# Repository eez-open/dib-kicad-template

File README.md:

### KiCad project template for EEZ DIB peripheral modules

The project template makes it easy to start working on a new peripheral module and will need to be copied to your local KiCad template folder.

The template was created using symbols, footprints and 3D models from [eez-kicad-libraries](https://github.com/eez-open/eez-kicad-libraries), so for proper display it is recommended to install that plugin.

### Setting up the KiCad template folder

Start KiCad and in `Preferences` (1) open `Configure Paths...` (2) where you can see the currently configured Template path that you can change as desired.

### Copying a template and creating a new project from the template

Copy the complete contents of the template folder from this repository into it (e.g. `v2.0`)

Now you are ready to use the EEZ DIB template for your new project. To do this, you will need to select the `New Project...` option from the `File` menu (3).

Select `User Templates`, and find the EEZ DIB template (4) and confirm the selection with `OK` (5).

### Setting project text variables

The new project is created and you can change the predefined texts as desired by first opening the `Schematic Editor` (6).

In the `File` menu of the Schematic Editor, select the option `Schematic Setup...` (7) and under `Text Variables` (8) you can see the values ​​of the text variables that were used and change them as desired.

Good luck and we wish you successful development. Feel free to keep us updated on your progress and contact us if you need further help with the EEZ DIB!

### About KiCad

KiCad is a Cross-Platform free and Open Source Electronics Design Automation Suite. See [KiCad EDA](https://kicad.org/) for more information.

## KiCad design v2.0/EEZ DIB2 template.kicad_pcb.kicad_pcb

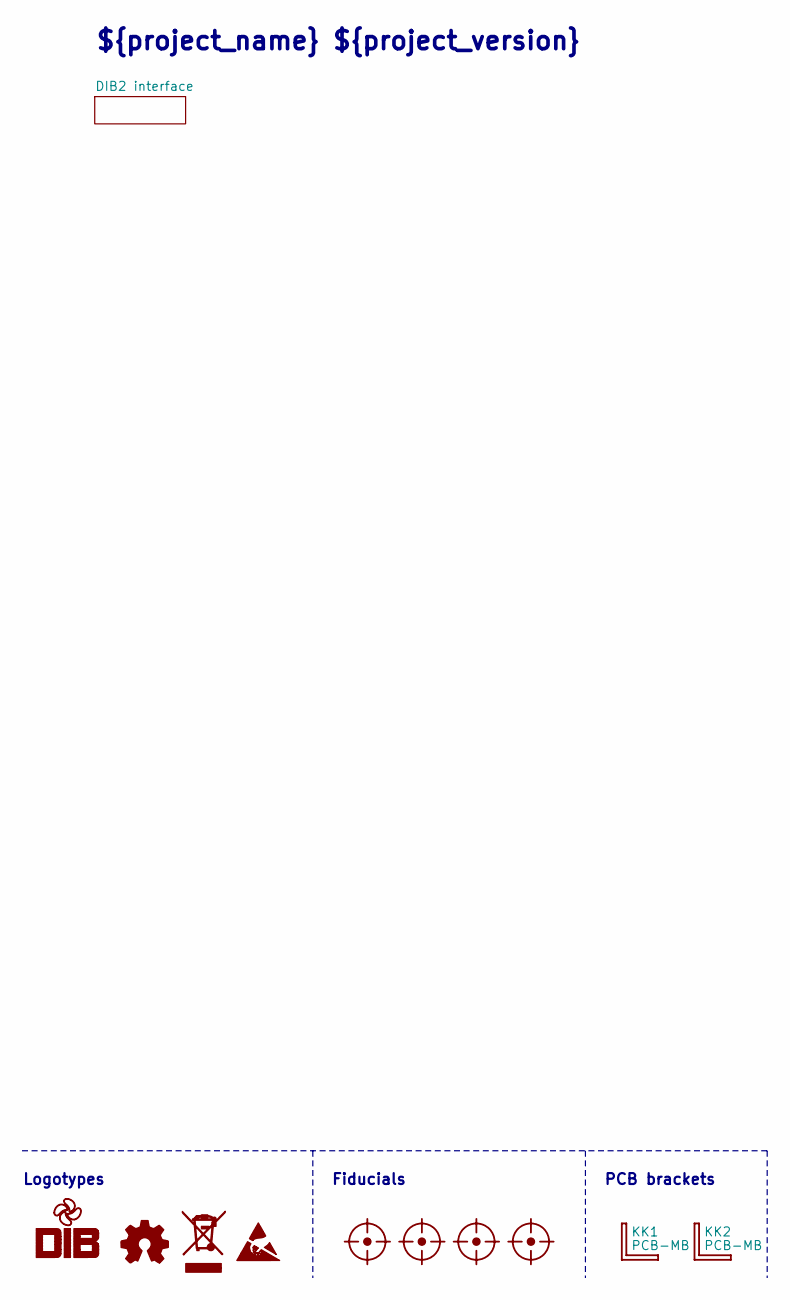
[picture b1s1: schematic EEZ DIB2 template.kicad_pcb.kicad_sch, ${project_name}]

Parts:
FM1, FM2, FM3, FM4: FIDUCIAL_2; Fiducial_0.75mm_Mask1.5mm
KK1, KK2: PCB-MB; PCB-MB-01; DigiKey RPC1760-ND
LOGO1: EEZ DIB logo; EEZ DIB logo (9mm)
LOGO2: Open HW logo
LOGO3: WEEE logo
LOGO4: ESD logo

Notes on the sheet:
${project_name} ${project_version}
PCB brackets
Logotypes
Fiducials

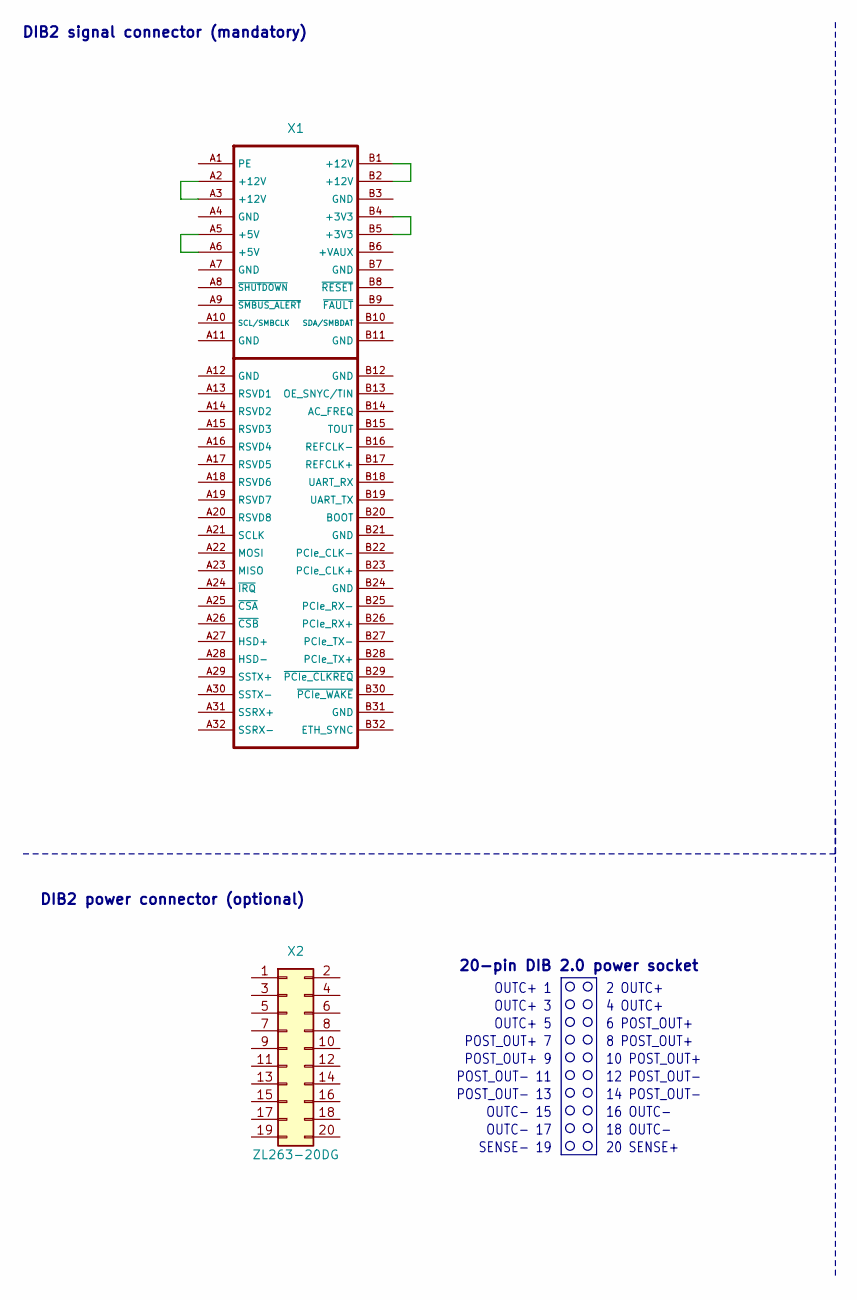
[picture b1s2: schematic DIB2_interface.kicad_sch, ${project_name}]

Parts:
X1: DIB 2.0 signal connector; DIB 2.0 edge card connector
X2: ZL263-20DG; SSW-110-02-T-D-RA; DigiKey SAM10030-ND

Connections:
unnamed: X1.B4 (+3V3), X1.B5 (+3V3)
unnamed: X1.A5 (+5V), X1.A6 (+5V)
unnamed: X1.A2 (+12V), X1.A3 (+12V)
unnamed: X1.B1 (+12V), X1.B2 (+12V)

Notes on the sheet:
16 OUTC-
OUTC+ 3
OUTC+ 5
POST_OUT- 13
14 POST_OUT-
DIB2 signal connector (mandatory)
POST_OUT+ 7
12 POST_OUT-
POST_OUT+ 9
POST_OUT- 11
OUTC+ 1
4 OUTC+
OUTC- 17
20-pin DIB 2.0 power socket
OUTC- 15
20 SENSE+
SENSE- 19
6 POST_OUT+
8 POST_OUT+
10 POST_OUT+
18 OUTC-
DIB2 power connector (optional)
2 OUTC+

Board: 4 copper layers, 12 parts (0 on the bottom side), 4 nets, no tracks yet.

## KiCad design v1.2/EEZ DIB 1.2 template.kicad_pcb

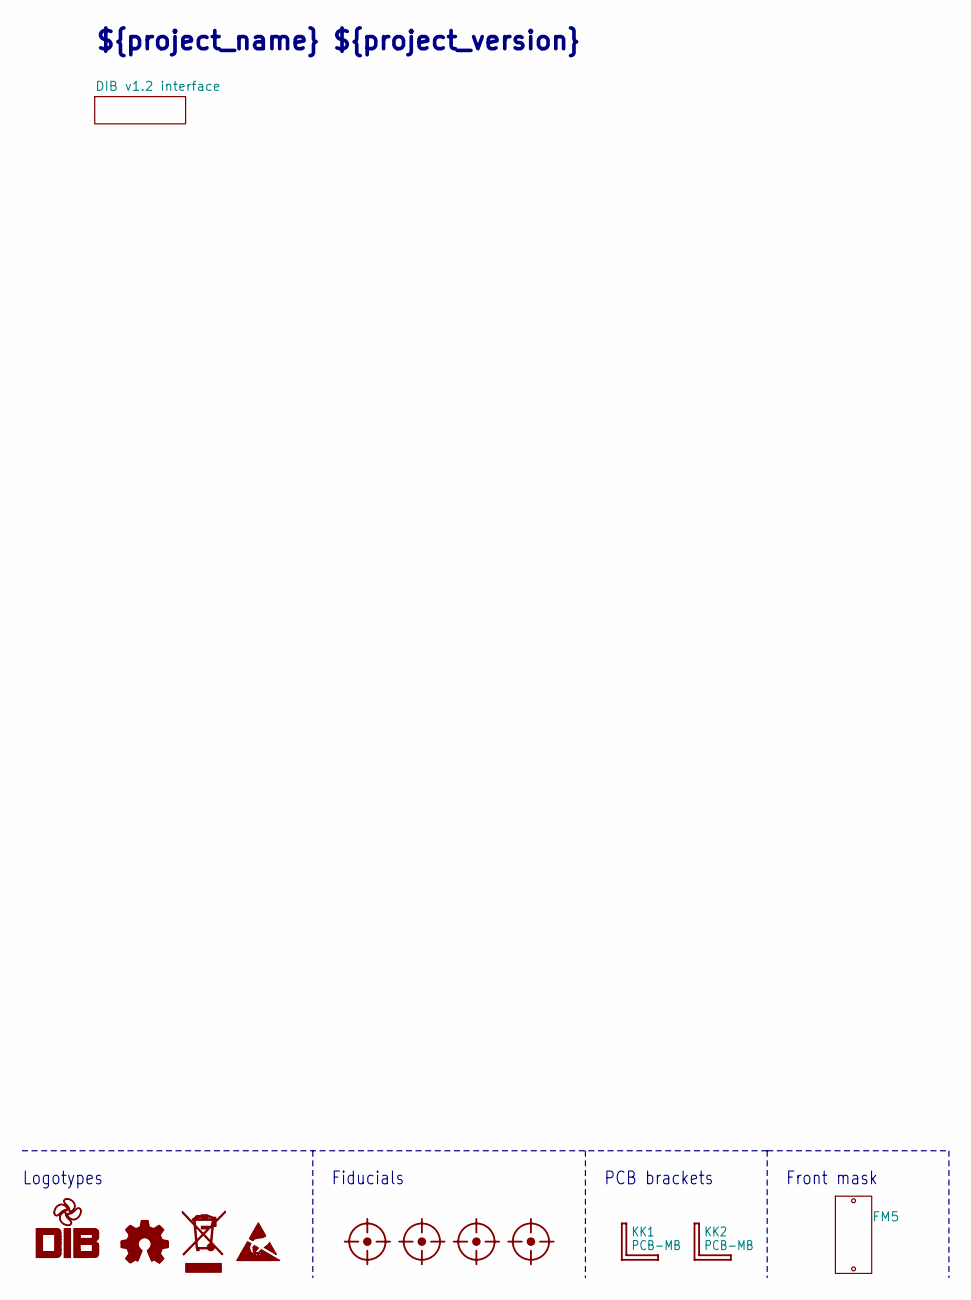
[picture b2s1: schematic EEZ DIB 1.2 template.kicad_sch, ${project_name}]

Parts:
FM1, FM2, FM3, FM4: FIDUCIAL_2; Fiducial
FM5: DIB module front mask
KK1, KK2: PCB-MB; PCB-MB-01; DigiKey RPC1760-ND
LOGO1: EEZ DIB logo; EEZ DIB logo (9mm)
LOGO2: Open HW logo
LOGO3: WEEE logo
LOGO4: ESD logo

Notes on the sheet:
${project_name} ${project_version}
PCB brackets
Logotypes
Fiducials
Front mask

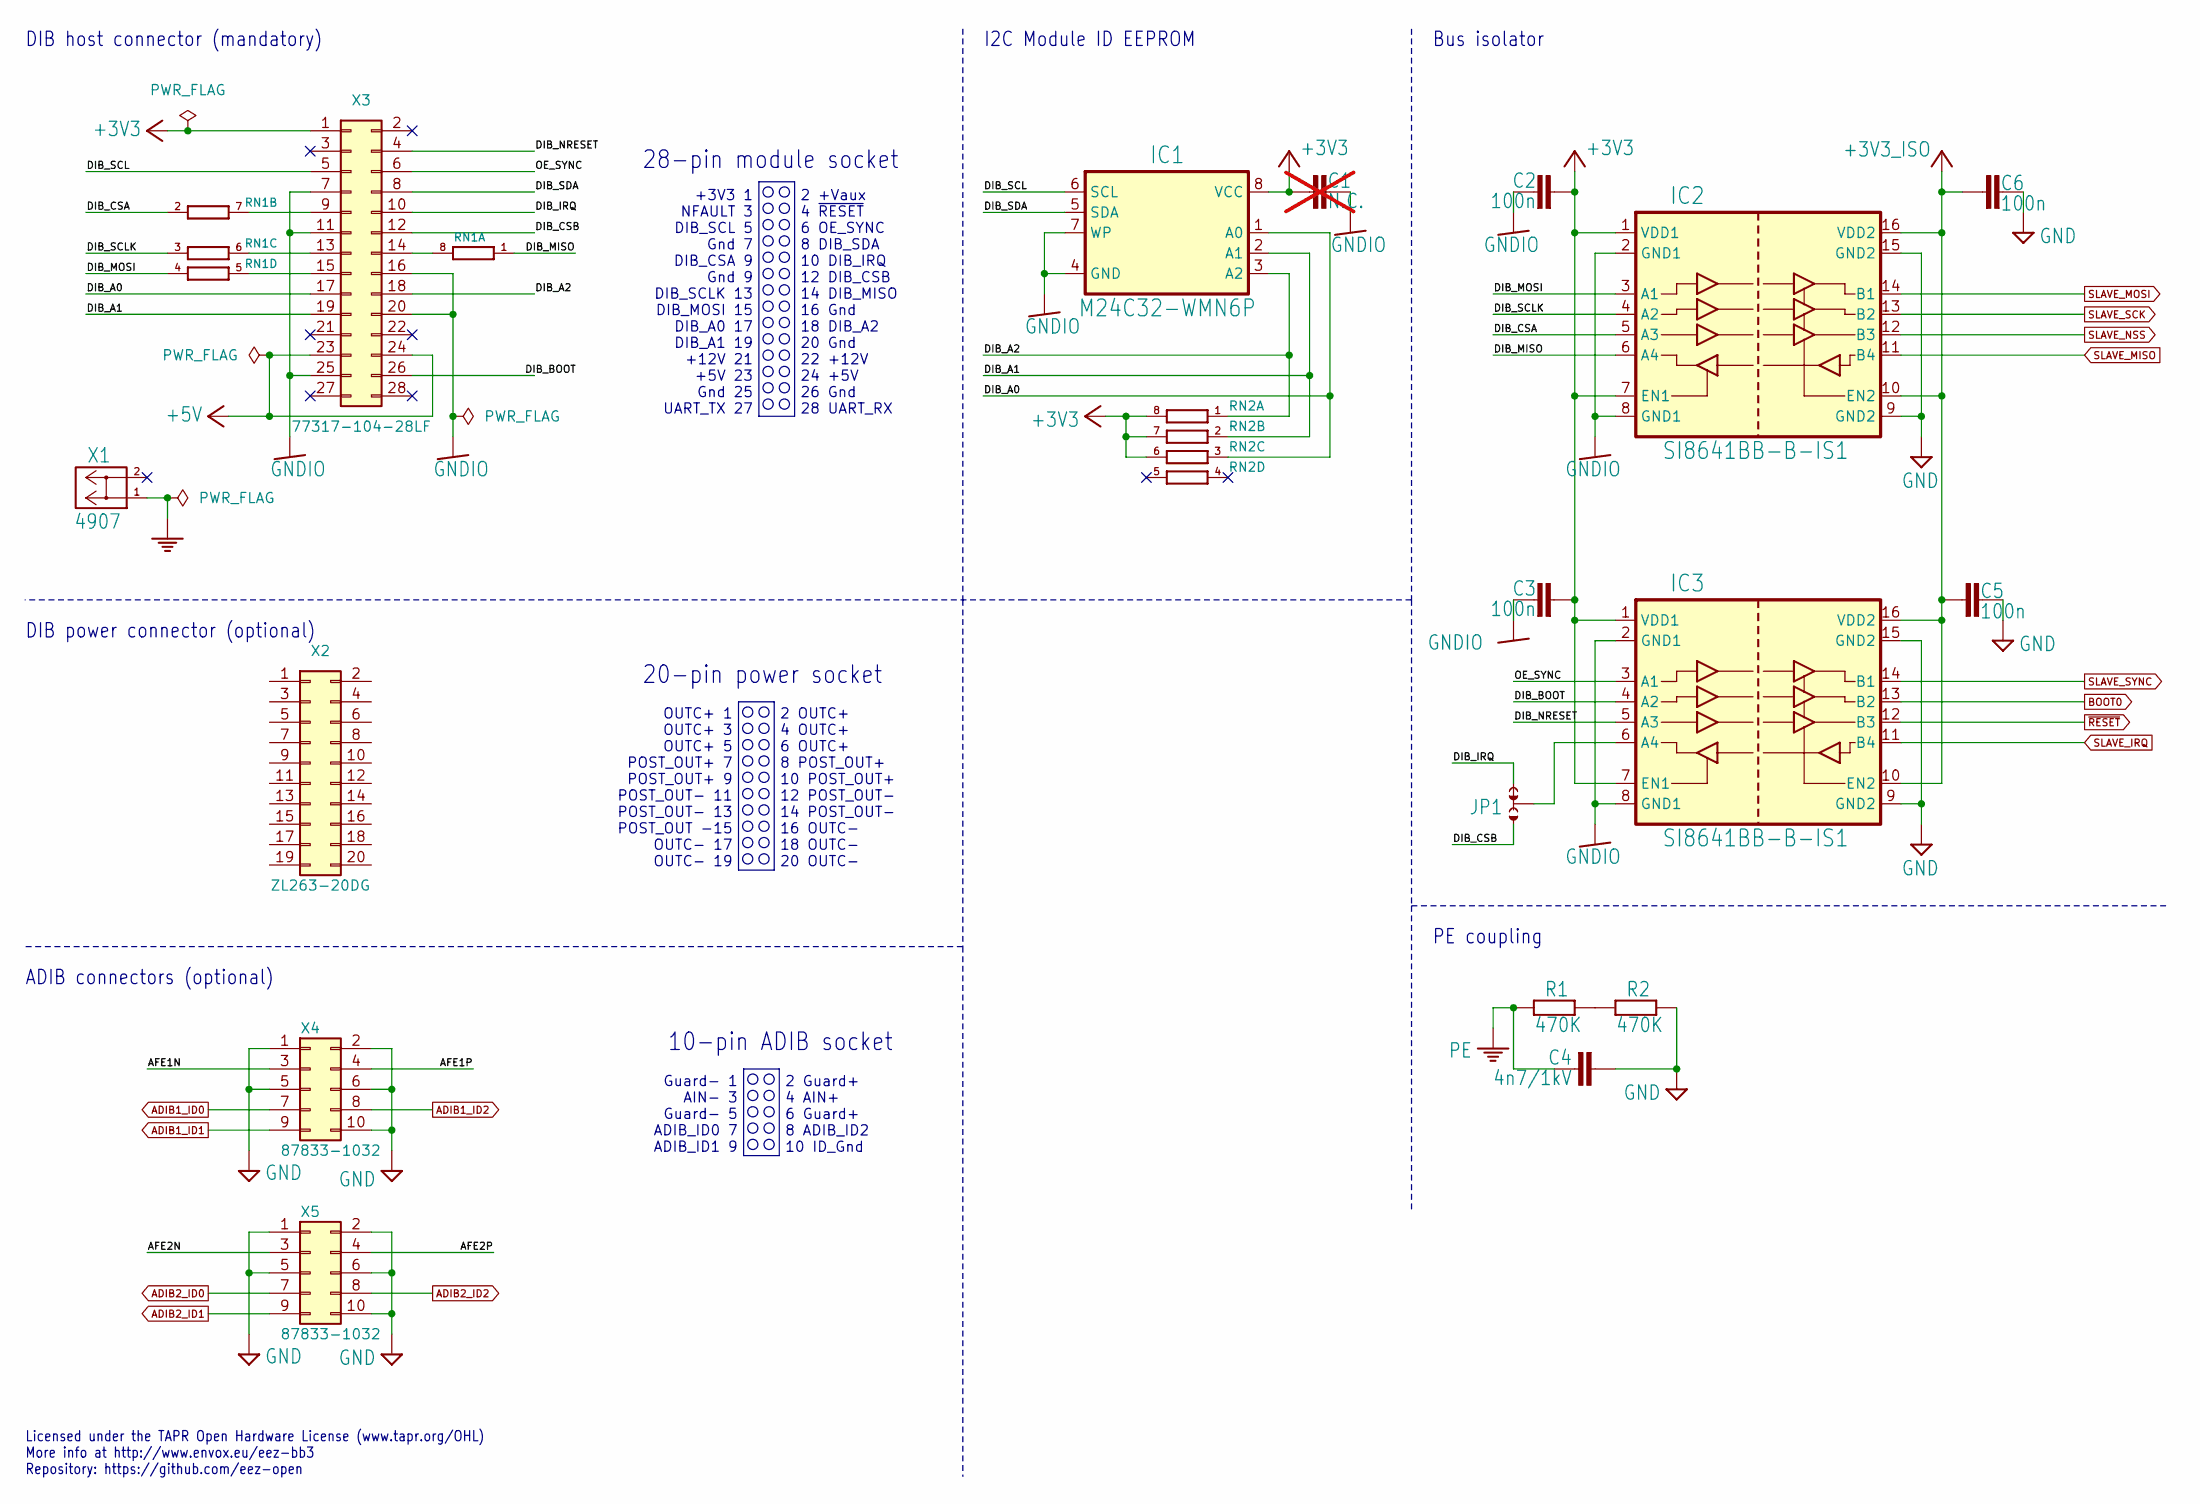
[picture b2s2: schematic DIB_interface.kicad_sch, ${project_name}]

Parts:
C1: N.C.; C_0603_1608Metric; not fitted
C2, C3, C5, C6: 100n; C_0603_1608Metric; DigiKey 1276-1005-2-ND
C4: 4n7/1kV; C_1206_3216Metric; DigiKey 732-12074-2-ND
IC1: M24C32-WMN6P; SOIC127P600X173-8N; DigiKey 497-8572-5-ND
IC2, IC3: SI8641BB-B-IS1; SOIC127P600X265-16N; DigiKey 336-2566-ND
JP1: JP3-CUT-0805-ROTATED; JP3 shorted
R1, R2: 470K; R_0805_2012Metric; DigiKey 13-RT0805FRE07470KLDKR-ND
RN1: DR1206-33R-4/8; CAY16; DigiKey CAY16-330J4LFCT-ND
RN2: DR1206-47K-4/8; CAY16; DigiKey CAY16-330J4LFCT-ND
X1: 4907; DigiKey 36-4907-ND
X2: ZL263-20DG; SSW-110-02-T-D-RA; DigiKey SAM10030-ND
X3: 77317-104-28LF; DigiKey S2111EC-14-ND
X4, X5: 87833-1032; DS1014-10RF1B; DigiKey WM8615-ND

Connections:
+3V3: C1.2, C2.1, C3.1, IC1.8 (VCC), IC2.1 (VDD1), IC2.7 (EN1), IC3.1 (VDD1), IC3.7 (EN1), RN2.6 (2), RN2.7 (2), RN2.8 (2), X3.1
+3V3_ISO: C5.2, C6.2, IC2.10 (EN2), IC2.16 (VDD2), IC3.10 (EN2), IC3.16 (VDD2)
+5V: X3.23, X3.24
/DIB v1.2 interface/AFE1N: X4.3
/DIB v1.2 interface/AFE1P: X4.4
/DIB v1.2 interface/AFE2N: X5.3
/DIB v1.2 interface/AFE2P: X5.4
/DIB v1.2 interface/DIB_A0: IC1.1 (A0), RN2.3 (1), X3.17
/DIB v1.2 interface/DIB_A1: IC1.2 (A1), RN2.2 (1), X3.19
/DIB v1.2 interface/DIB_A2: IC1.3 (A2), RN2.1, X3.18
/DIB v1.2 interface/DIB_BOOT: IC3.4 (A2), X3.26
/DIB v1.2 interface/DIB_CSA: IC2.5 (A3), RN1.2 (1)
/DIB v1.2 interface/DIB_CSB: JP1.NO, X3.12
/DIB v1.2 interface/DIB_IRQ: JP1.NC, X3.10
/DIB v1.2 interface/DIB_MISO: IC2.6 (A4), RN1.1
/DIB v1.2 interface/DIB_MOSI: IC2.3 (A1), RN1.4 (1)
/DIB v1.2 interface/DIB_NRESET: IC3.5 (A3), X3.4
/DIB v1.2 interface/DIB_SCL: IC1.6 (SCL), X3.5
/DIB v1.2 interface/DIB_SCLK: IC2.4 (A2), RN1.3 (1)
/DIB v1.2 interface/DIB_SDA: IC1.5 (SDA), X3.8
/DIB v1.2 interface/OE_SYNC: IC3.3 (A1), X3.6
ADIB1_ID0: X4.7
ADIB1_ID1: X4.9
ADIB1_ID2: X4.8
ADIB2_ID0: X5.7
ADIB2_ID1: X5.9
ADIB2_ID2: X5.8
BOOT0: IC3.13 (B2)
GND: C4.2, C5.1, C6.1, IC2.9 (GND2), IC2.15 (GND2), IC3.9 (GND2), IC3.15 (GND2), R2.2, X4.1, X4.2, X4.5, X4.6, X4.10, X5.1, X5.2, X5.5, X5.6, X5.10
GNDIO: C1.1, C2.2, C3.2, IC1.4 (GND), IC1.7 (WP), IC2.2 (GND1), IC2.8 (GND1), IC3.2 (GND1), IC3.8 (GND1), X3.7, X3.11, X3.16, X3.20, X3.25
unnamed: IC3.6 (A4), JP1.COM
unnamed: R1.2, R2.1
unnamed: RN1.8 (2), X3.14
unnamed: RN1.7 (2), X3.9
unnamed: RN1.6 (2), X3.13
unnamed: RN1.5 (2), X3.15
PE: C4.1, R1.1, X1.1
SLAVE_IRQ: IC3.11 (B4)
SLAVE_MISO: IC2.11 (B4)
SLAVE_MOSI: IC2.14 (B1)
SLAVE_NSS: IC2.12 (B3)
SLAVE_SCK: IC2.13 (B2)
SLAVE_SYNC: IC3.14 (B1)
~RESET: IC3.12 (B3)

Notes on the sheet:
OUTC+ 1 OUTC+ 3 OUTC+ 5 POST_OUT+ 7 POST_OUT+ 9 POST_OUT- 11 POST_OUT- 13 POST_OUT -15 OUTC- 17 OUTC- 19
28-pin module socket
DIB host connector (mandatory)
Licensed under the TAPR Open Hardware License (www.tapr.org/OHL) More info at http://www.envox.eu/eez-bb3 Repository: https://github.com/eez-open
PE coupling
2 +Vaux 4 ~{RESET} 6 OE_SYNC 8 DIB_SDA 10 DIB_IRQ 12 DIB_CSB 14 DIB_MISO 16 Gnd 18 DIB_A2 20 Gnd 22 +12V 24 +5V 26 Gnd 28 UART_RX
+3V3 1 NFAULT 3 DIB_SCL 5 Gnd 7 DIB_CSA 9 Gnd 9 DIB_SCLK 13 DIB_MOSI 15 DIB_A0 17 DIB_A1 19 +12V 21 +5V 23 Gnd 25 UART_TX 27
ADIB connectors (optional)
2 OUTC+ 4 OUTC+ 6 OUTC+ 8 POST_OUT+ 10 POST_OUT+ 12 POST_OUT- 14 POST_OUT- 16 OUTC- 18 OUTC- 20 OUTC-
10-pin ADIB socket
2 Guard+ 4 AIN+ 6 Guard+ 8 ADIB_ID2 10 ID_Gnd
DIB power connector (optional)
I2C Module ID EEPROM
20-pin power socket
Guard- 1 AIN- 3 Guard- 5 ADIB_ID0 7 ADIB_ID1 9
Bus isolator

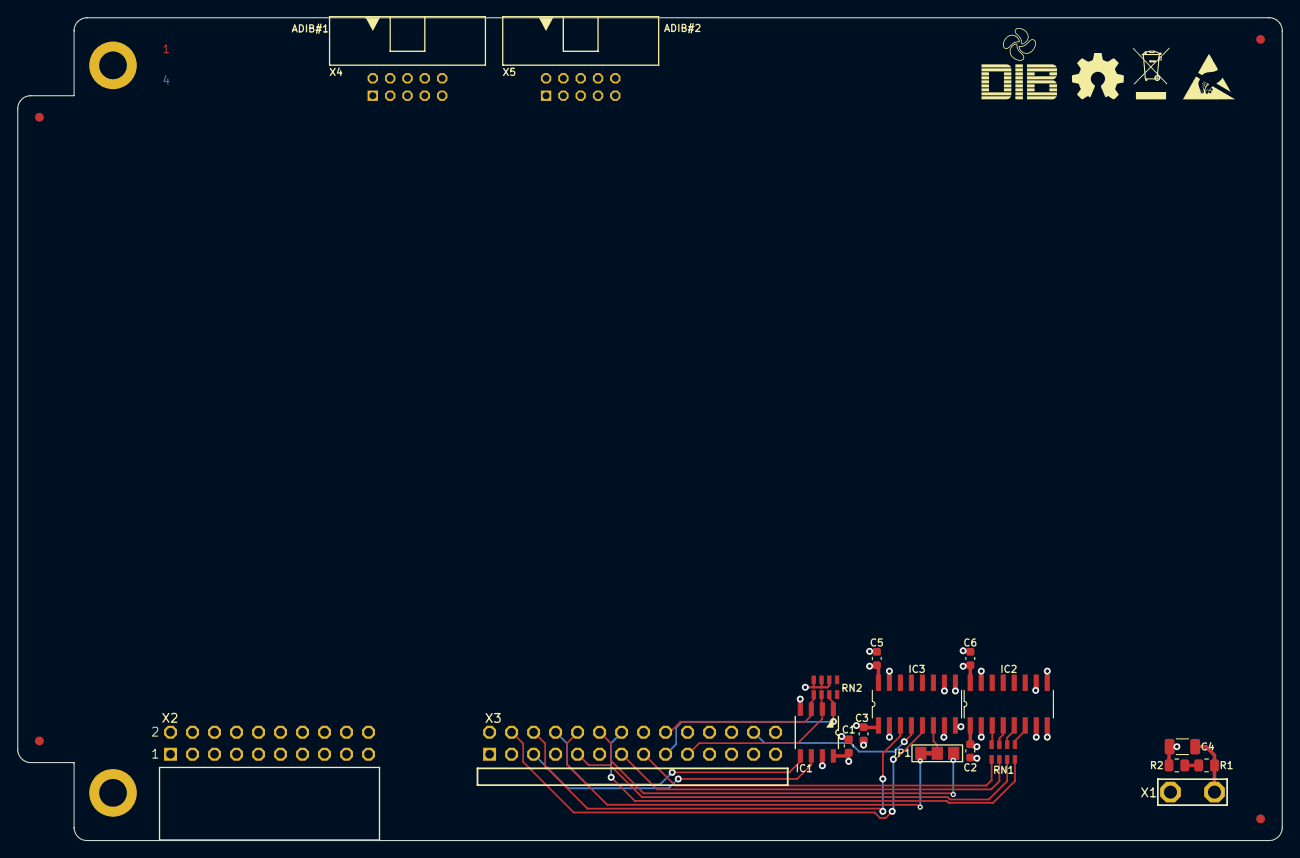
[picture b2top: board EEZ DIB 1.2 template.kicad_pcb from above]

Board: 4 copper layers, 146.0 x 95.0 mm, 30 parts (0 on the bottom side), 26 nets.

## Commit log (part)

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2024-12-15 Power DIB connector added
2024-12-15 Resize 3D preview
2024-12-15 Set Text variables
2024-12-16 README.md update
2025-02-04 BOM update
2025-02-06 3D model updated
